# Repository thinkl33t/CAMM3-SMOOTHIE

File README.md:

Project to replace the mainboard of a CAMM3 with a smoothieboard.
=================================================================

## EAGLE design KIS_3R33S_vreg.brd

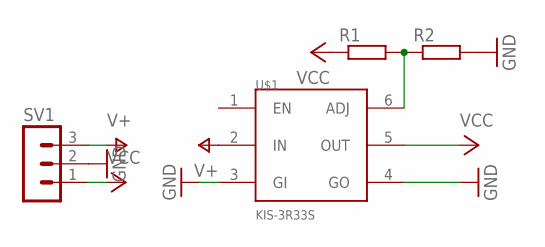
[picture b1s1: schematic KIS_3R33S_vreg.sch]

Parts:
R1, R2: R-EU_R1206W; R1206W
SV1: MA03-1
U$1: KIS-3R33S

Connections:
GND: R2.2, SV1.2, U$1.3 (GI), U$1.4 (GO)
unnamed: R1.2, R2.1, U$1.6 (ADJ)
V+: SV1.3, U$1.2 (IN)
VCC: R1.1, SV1.1, U$1.5 (OUT)

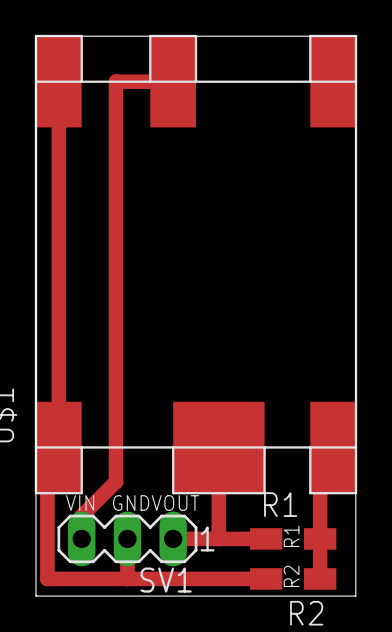
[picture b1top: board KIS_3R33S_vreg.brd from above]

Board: 2 copper layers, 17.8 x 31.1 mm, 4 parts (0 on the bottom side), 4 nets.

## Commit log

2014-05-13 Added CAMM3 files and Smoothie Data
2014-05-14 Added RJ11 breakout v0.1
2014-05-15 changed to correct RJ11 part
2014-06-22 New RJ11 breakout
2014-06-22 Made sure RJ11 breakout was usable, added rj45 breakout
2014-06-22 Added PNG and vector version of the mainboard, v1 of mounting plate
2014-06-25 Added Gobotics' KIS3R33S 78BXX Power Regulator
